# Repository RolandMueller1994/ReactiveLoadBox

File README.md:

# ReactiveLoadBox

This repository contains the design of a reactive load box for guitar amplifiers. The intention is to match the impedance of a 1x12 vented guitar cabinet closely to achieve good recreation of the cabinets frequency response via impulse responses (IRs).

## Simulation

Simulation is primarily executed via Python scripts that analyze the measurement results and calculate the circuit's impedance from config values.
Based on the measured and simulated data, the input power and level to the cabinet and the circuit are calculated.

The measured and calculated impedance is shown below.

Cabinet and load input power is shown in below.

The power dissipation in each circuit component is displayed in following figure.

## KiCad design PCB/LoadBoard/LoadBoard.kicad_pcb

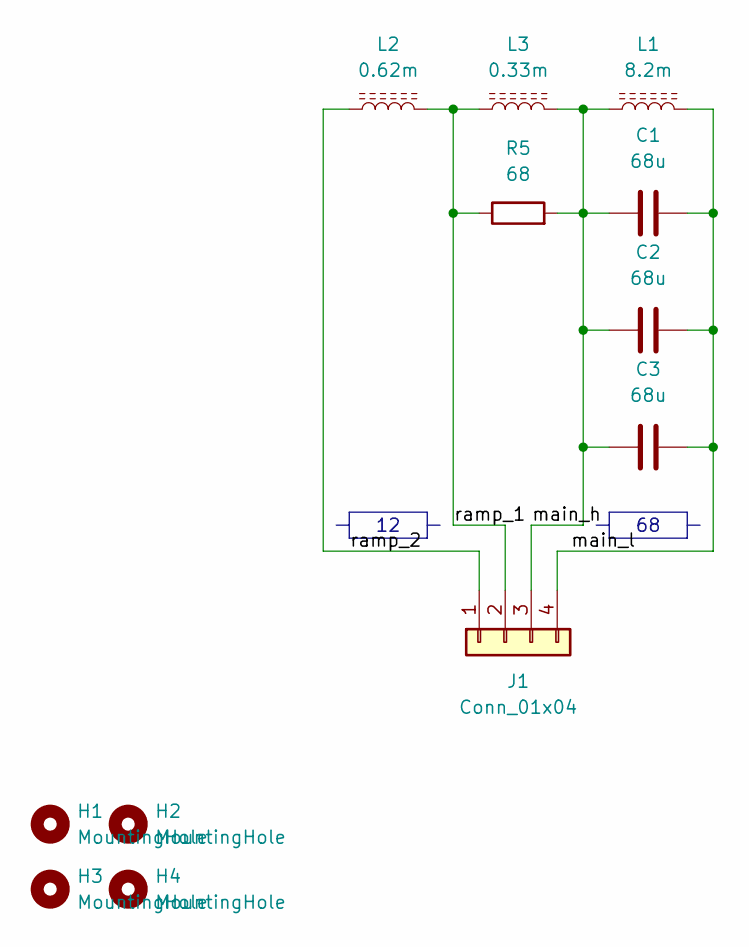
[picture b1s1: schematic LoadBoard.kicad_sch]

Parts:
C1, C2, C3: 68u; ERA_68_100_1
H1, H2, H3, H4: MountingHole; MountingHole_3.2mm_M3
J1: Conn_01x04; TerminalBlock_Phoenix_MKDS-1-4-3.81_1x04_P3.81mm_Horizontal
L1: 8.2m; DR56_8m2_095
L2: 0.62m; LU44_100
L3: 0.33m; LU44_100
R5: 68; R_Axial_Power_L60.0mm_W14.0mm_P66.04mm

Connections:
/main_h: C1.1, C2.1, C3.1, J1.3, L1.1, L3.2, R5.2
/main_l: C1.2, C2.2, C3.2, J1.4, L1.2
/ramp_1: J1.2, L2.2, L3.1, R5.1
/ramp_2: J1.1, L2.1

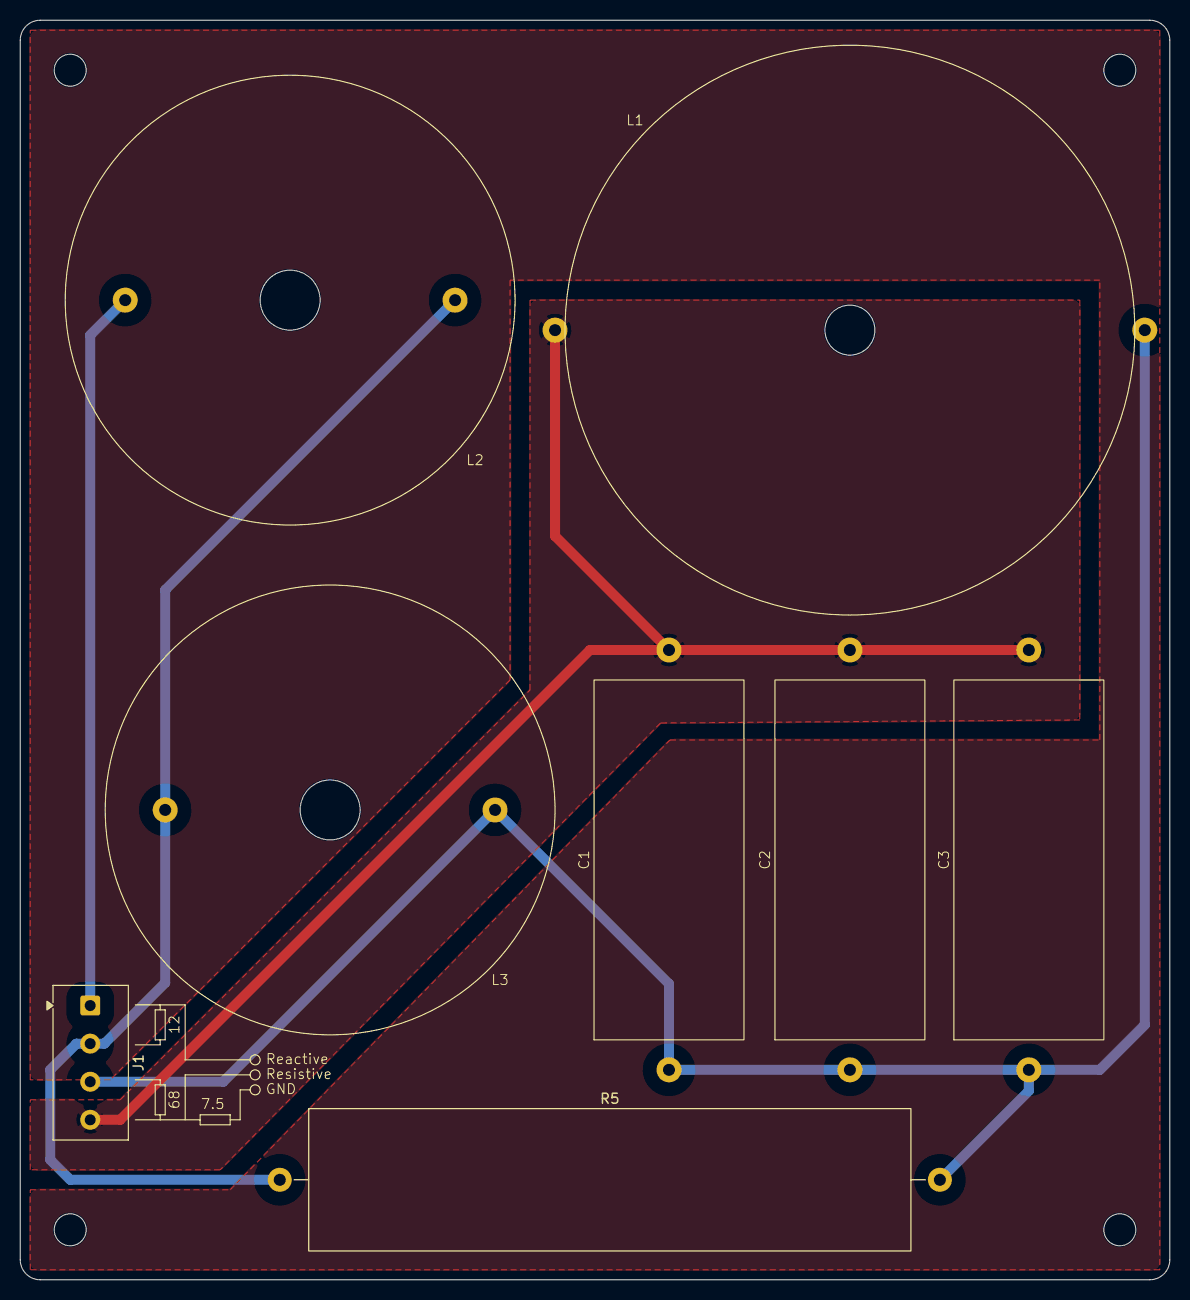
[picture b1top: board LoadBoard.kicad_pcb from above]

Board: 2 copper layers, 115.0 x 126.0 mm, 12 parts (0 on the bottom side), 4 nets.

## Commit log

2026-04-05 Add impedance measurement
2026-04-05 Add first version of python script to calculate impedance curve
2026-04-05 Rearrange plots and add export. Change config values slightly
2026-05-05 Added power calculation
2026-05-06 Input power calculation
2026-05-06 Fixed power calculation
2026-05-06 Added max power function
2026-05-06 Fixed power calculation of secondary ramp impedance
2026-05-07 Added level calculation
2026-05-08 Added power analysis for measured impedance
2026-05-08 Add license
2026-05-12 Start load board and 3d modeling
2026-05-12 Cleanup
2026-05-13 Layout of load pcb
